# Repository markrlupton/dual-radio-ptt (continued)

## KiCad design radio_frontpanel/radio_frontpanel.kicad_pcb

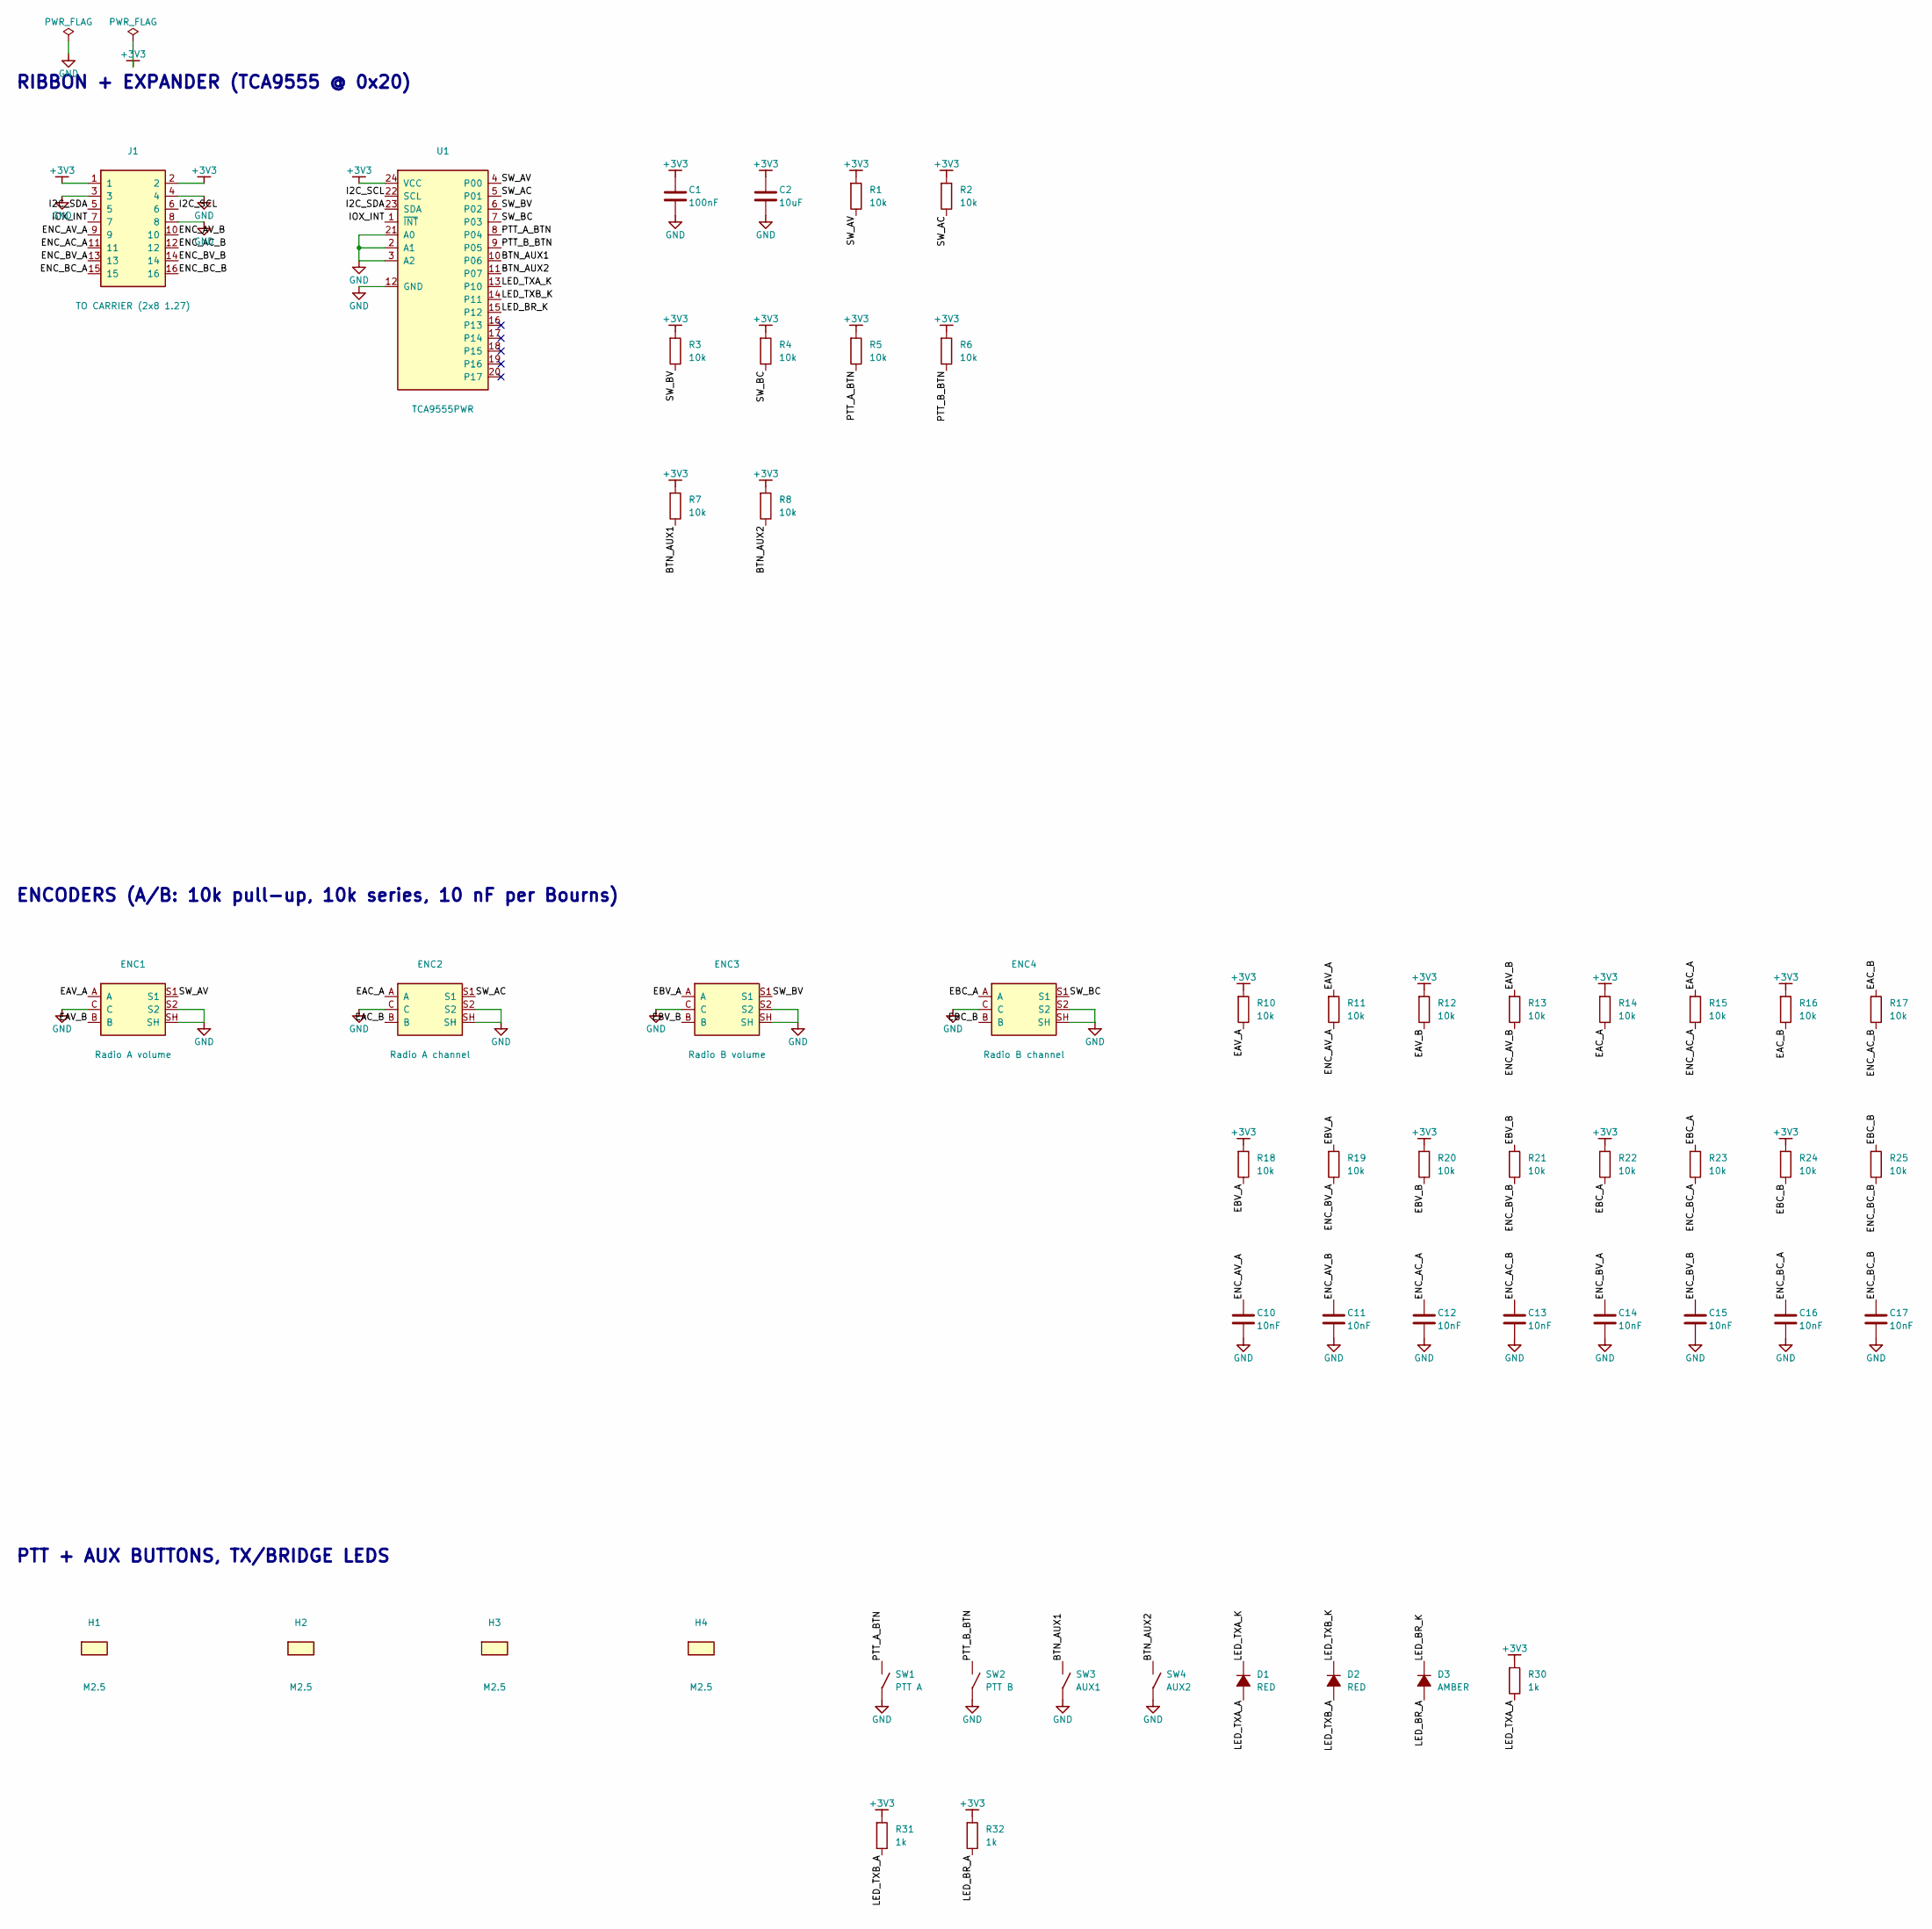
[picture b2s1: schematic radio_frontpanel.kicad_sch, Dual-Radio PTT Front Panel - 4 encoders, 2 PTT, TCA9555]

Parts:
C1: 100nF; C_0603_1608Metric; MPN 0603 X7R 16V; LCSC C14663
C2: 10uF; C_0805_2012Metric; MPN 0805 X7R 16V; LCSC C15850
C10, C11, C12, C13, C14, C15, C16, C17: 10nF; C_0603_1608Metric; MPN 0603 X7R 16V; LCSC C57112
D1, D2: RED; LED_0805_2012Metric; MPN 0805 red LED; LCSC C84256
D3: AMBER; LED_0805_2012Metric; MPN NationStar NCD0805O1 (amber/orange 605 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; LCSC C84262
ENC1: Radio A volume; RotaryEncoder_Bourns_Vertical_PEC12R-3x17F-Sxxxx; MPN Bourns PEC12R-4217F-S0024 (17 mm flatte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; LCSC C49671241
ENC2: Radio A channel; RotaryEncoder_Bourns_Vertical_PEC12R-3x17F-Sxxxx; MPN Bourns PEC12R-4217F-S0024 (17 mm flatte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; LCSC C49671241
ENC3: Radio B volume; RotaryEncoder_Bourns_Vertical_PEC12R-3x17F-Sxxxx; MPN Bourns PEC12R-4217F-S0024 (17 mm flatte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; LCSC C49671241
ENC4: Radio B channel; RotaryEncoder_Bourns_Vertical_PEC12R-3x17F-Sxxxx; MPN Bourns PEC12R-4217F-S0024 (17 mm flatte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; LCSC C49671241
H1, H2, H3, H4: M2.5; MountingHole_2.7mm_M2.5
J1: TO CARRIER (2x8 1.27); PinHeader_2x08_P1.27mm_Vertical; MPN 2x8 1.27 mm header
R1, R2, R3, R4, R5, R6, R7, R8, R10, R11, R12, R13, R14, R15, R16, R17, R18, R19, R20, R21, R22, R23, R24, R25: 10k; R_0603_1608Metric; MPN 0603 1% resistor; LCSC C25804
R30, R31, R32: 1k; R_0603_1608Metric; MPN 0603 1% resistor; LCSC C21190
SW1: PTT A; SW_PUSH-12mm; MPN 12 mm tactile switch
SW2: PTT B; SW_PUSH-12mm; MPN 12 mm tactile switch
SW3: AUX1; SW_PUSH_6mm; MPN 6 mm tactile switch
SW4: AUX2; SW_PUSH_6mm; MPN 6 mm tactile switch
U1: TCA9555PWR; TSSOP-24_4.4x7.8mm_P0.65mm; MPN TI TCA9555PWR; LCSC C465732

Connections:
+3V3: C1.1, C2.1, J1.1, J1.2, R1.1, R2.1, R3.1, R4.1, R5.1, R6.1, R7.1, R8.1, R10.1, R12.1, R14.1, R16.1, R18.1, R20.1, R22.1, R24.1, R30.1, R31.1, R32.1, U1.24 (VCC)
BTN_AUX1: R7.2, SW3.1, U1.10 (P06)
BTN_AUX2: R8.2, SW4.1, U1.11 (P07)
EAC_A: ENC2.A, R14.2, R15.1
EAC_B: ENC2.B, R16.2, R17.1
EAV_A: ENC1.A, R10.2, R11.1
EAV_B: ENC1.B, R12.2, R13.1
EBC_A: ENC4.A, R22.2, R23.1
EBC_B: ENC4.B, R24.2, R25.1
EBV_A: ENC3.A, R18.2, R19.1
EBV_B: ENC3.B, R20.2, R21.1
ENC_AC_A: C12.1, J1.11, R15.2
ENC_AC_B: C13.1, J1.12, R17.2
ENC_AV_A: C10.1, J1.9, R11.2
ENC_AV_B: C11.1, J1.10, R13.2
ENC_BC_A: C16.1, J1.15, R23.2
ENC_BC_B: C17.1, J1.16, R25.2
ENC_BV_A: C14.1, J1.13, R19.2
ENC_BV_B: C15.1, J1.14, R21.2
GND: C1.2, C2.2, C10.2, C11.2, C12.2, C13.2, C14.2, C15.2, C16.2, C17.2, ENC1.C, ENC1.S2, ENC1.SH, ENC2.C, ENC2.S2, ENC2.SH, ENC3.C, ENC3.S2, ENC3.SH, ENC4.C, ENC4.S2, ENC4.SH, J1.3, J1.4, J1.8, SW1.2, SW2.2, SW3.2, SW4.2, U1.2 (A1), U1.3 (A2), U1.12 (GND), U1.21 (A0)
I2C_SCL: J1.6, U1.22 (SCL)
I2C_SDA: J1.5, U1.23 (SDA)
IOX_INT: J1.7, U1.1 (~INT)
LED_BR_A: D3.2 (A), R32.2
LED_BR_K: D3.1 (K), U1.15 (P12)
LED_TXA_A: D1.2 (A), R30.2
LED_TXA_K: D1.1 (K), U1.13 (P10)
LED_TXB_A: D2.2 (A), R31.2
LED_TXB_K: D2.1 (K), U1.14 (P11)
PTT_A_BTN: R5.2, SW1.1, U1.8 (P04)
PTT_B_BTN: R6.2, SW2.1, U1.9 (P05)
SW_AC: ENC2.S1, R2.2, U1.5 (P01)
SW_AV: ENC1.S1, R1.2, U1.4 (P00)
SW_BC: ENC4.S1, R4.2, U1.7 (P03)
SW_BV: ENC3.S1, R3.2, U1.6 (P02)

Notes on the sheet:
RIBBON + EXPANDER (TCA9555 @ 0x20)
ENCODERS (A/B: 10k pull-up, 10k series, 10 nF per Bourns)
PTT + AUX BUTTONS, TX/BRIDGE LEDS

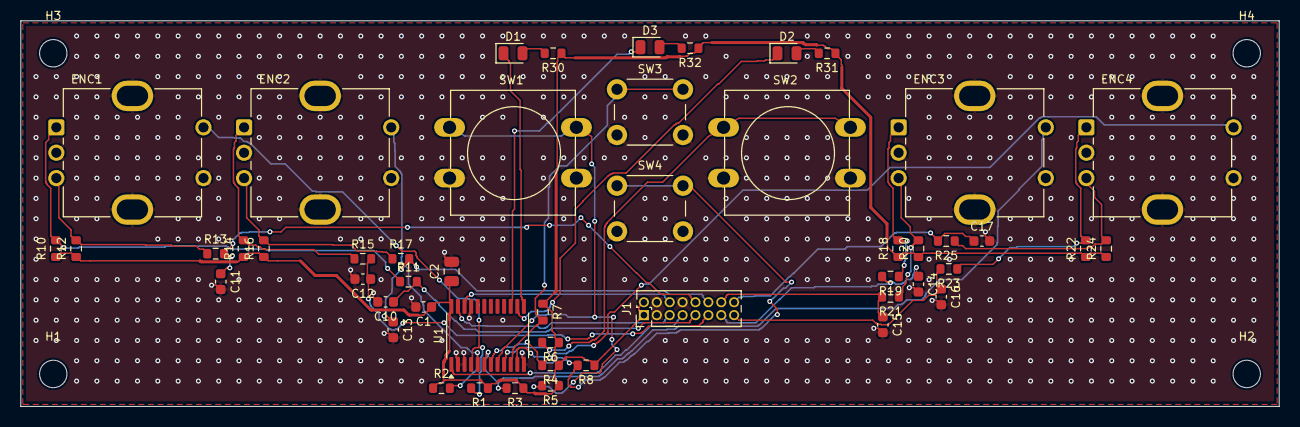
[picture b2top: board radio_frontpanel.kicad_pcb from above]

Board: 4 copper layers, 124.0 x 38.0 mm, 54 parts (0 on the bottom side), 35 nets.

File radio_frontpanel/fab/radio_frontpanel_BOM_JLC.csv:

Comment,Designator,Footprint,LCSC Part #
100nF,C1,C_0603_1608Metric,C14663
10uF,C2,C_0805_2012Metric,C15850
10nF,"C10,C11,C12,C13,C14,C15,C16,C17",C_0603_1608Metric,C57112
RED,"D1,D2",LED_0805_2012Metric,C84256
NCD0805O1,D3,LED_0805_2012Metric,C84262
PEC12R-4217F-S0024,ENC1,RotaryEncoder_Bourns_Vertical_PEC12R-3x17F-Sxxxx,C49671241
PEC12R-4217F-S0024,ENC2,RotaryEncoder_Bourns_Vertical_PEC12R-3x17F-Sxxxx,C49671241
PEC12R-4217F-S0024,ENC3,RotaryEncoder_Bourns_Vertical_PEC12R-3x17F-Sxxxx,C49671241
PEC12R-4217F-S0024,ENC4,RotaryEncoder_Bourns_Vertical_PEC12R-3x17F-Sxxxx,C49671241
TO CARRIER (2x8 1.27),J1,PinHeader_2x08_P1.27mm_Vertical,
10k,"R1,R2,R3,R4,R5,R6,R7,R8,R10,R11,R12,R13,R14,R15,R16,R17,R18,R19,R20,R21,R22,R23,R24,R25",R_0603_1608Metric,C25804
1k,"R30,R31,R32",R_0603_1608Metric,C21190
PTT A,SW1,SW_PUSH-12mm,
PTT B,SW2,SW_PUSH-12mm,
AUX1,SW3,SW_PUSH_6mm,
AUX2,SW4,SW_PUSH_6mm,
TCA9555PWR,U1,TSSOP-24_4.4x7.8mm_P0.65mm,C465732

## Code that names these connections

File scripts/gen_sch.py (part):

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    S.R(f"R{base+4}", "10", f"HP{ch}_OUT", "HS_SPK_L" if ch == "A" else "HS_SPK_R", "Output isolation")
S.C("C60", "330pF", "HPA_INV", "HPA_OUT", "HP LPF", diel="C0G"); S.C("C61", "330pF", "HPA_NI", "GND", "HP LPF mirror", diel="C0G")
S.C("C62", "330pF", "HPB_INV", "HPB_OUT", "HP LPF", diel="C0G"); S.C("C63", "330pF", "HPB_NI", "GND", "HP LPF mirror", diel="C0G")
S.R("R80", "100k", "HP_EN", "GND", "Amp held off until firmware drives HP_EN (Teensy pin 6)")
S.C("C65", "100nF", "+5VP", "GND", "U4 V+"); S.C("C66", "100nF", "-5VP", "GND", "U4 V-")
S.C("C67", "10uF", "+5VP", "GND", "U4 V+ bulk", "C0805"); S.C("C68", "10uF", "-5VP", "GND", "U4 V- bulk", "C0805")

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      "22": None, "23": None, "24": None, "25": "HUB_PWRJ", "26": "HUB_OVC", "27": None, "1": "GND",
      "16": "USBH_DP", "15": "USBH_DM", "11": "USB_B_DP", "10": "USB_B_DM", "9": "USB_A_DP", "8": "USB_A_DM",
      "7": None, "6": None, "5": None, "4": None}, "Terminus FE1.1S-BSOP28BCN", "C9359", "Self-powered (BUSJ high); ports 3/4 unused")
S.add("Y1", "Crystal_4pin", "12MHz", "XTAL", {"1": "HUB_XI", "3": "HUB_XO", "2": "GND", "4": "GND"}, "YXC X322512MSB4SI (12 MHz 3225, 20 pF, +/-10 ppm)", "C9002", "FE1.1s has internal load caps")
S.C("C80", "10pF", "HUB_XI", "GND", "Optional crystal load", diel="C0G", dnp=True); S.C("C81", "10pF", "HUB_XO", "GND", "Optional crystal load", diel="C0G", dnp=True)
S.R("R110", "2.7k", "HUB_REXT", "GND", "REXT 2.7k 1% (datasheet)")
S.R("R111", "10k", "HUB_3V3", "HUB_RST", "Reset pull-up"); S.C("C82", "100nF", "HUB_RST", "GND", "Reset RC")
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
